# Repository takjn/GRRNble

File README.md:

# GRRNble

DIY Smartwatch using Renesas RL78/G13 MCU and RN4020 ble module with Android companion app.

## Specification
### Hardware

- RL78/G13 32MHz (R5F100LJAFB 64pin LFQFP)
- ROM/RAM: 256KB/20KB
- 0.96″ 128x64 OLED display
- RN4020 Bluetooth Low Energy module
- RTC
- Buzzer
- Measuring battery voltage
- Li-Polymer Charging circuit

### Software

- Arduino like [IDE for GR](http://gadget.renesas.com/en/product/ide4gr.html) based smartwatch app
- [Android companion app](https://play.google.com/store/apps/details?id=com.github.takjn.grrnble)

## Hardware
### Schematic diagram
There is a KiCad project file in KiCad folder. Also, you can see the schematic pdf file in pdf folder.

### Parts list
All capacitors and resistors are 0805 (2012) SMD.

| Reference(s) | Value | Qty | Note |
|:---|:---|:---|:---|
|C1|0.47uF|1|I used 1.0uF insted.|
|C2, C11|0.1uF|2||
|C3, C4|15pF|2||
|C5, C6, C9, C10, C15, C16|1.0uF|6||
|C7, C12, C13|4.7uF|3||
|C8|2.2uF|1|I used 4.7uF insted.|
|R1|1k|1||
|R2|12k|1||
|R3|2k|1||
|R4|390k|1||
|R5, R6, R7, R13|10k|4||
|R8|22k|1||
|R9, R10|47k|2||
|R11|100k|1||
|R12, R14|100R|2||
|R15|7K5|1||
|R16|2K7|1||
|D1|CUS10F30|1||
|Q1, Q3|DMG3415U|2|P-ch FET|
|Q2|BSS138|1|N-ch FET|
|SW1, SW3, SW2|SKSCLAE010|3|ALPS Side Push switch|
|U1|R5F100LJAFB|1|RL78/G13 64pin|
|U2|UGCT7525AN4|1|Buzzer|
|U3|SSD1306|1|OLED 128x64 0.96 inch|
|U4|MCP73831-2-OT|1|Li-Polymer Charge Management Controller|
|U5|RN4020|1|Bluetooth Low Energy module|
|U6|MCP1703A-3302|1|LDO Regulator|
|Y1|FC-135|1|EPSON 3.2 x 1.5 x 0.80mm 32.768k crystal|
|BT1|Li-Po battery|1|3.7V/40mAh|
|J1|JST SH/1.0 6pin connector|1|JST 1.0mm pitch connector|
|-|JST SH/1.0 6pin cable|1|JST 1.0mm pitch terminal cable|
|-|FT232R / FT231X USB to serial adapter|1||

## Software

### RN4020 setup app

RN4020 can be setup with a special program and serial monitor.
Open RN4020Setup folder with [IDE for GR](http://gadget.renesas.com/en/product/ide4gr.html).
Connect your board and select GR-Cotton from "Tools" -> "Board" in the menu.
Compile the program and upload it to the board.

After uploading the sketch, select the port from "Tools" -> "Serial Port" in the menu and open Serial monitor.

### Smartwatch app

Open GRRNble folder with [IDE for GR](http://gadget.renesas.com/en/product/ide4gr.html).
Connect your board and select GR-Cotton from "Tools" -> "Board" in the menu.
Compile the program and upload it to the board.

### Android companion app

You need to have a development environment with Android Studio to build the Android App in the Android folder.

If you don't want to build from source files, you can install the compiled app from [Google Play](https://play.google.com/store/apps/details?id=com.github.takjn.grrnble).

## References
### Libraries
- [https://github.com/greiman/SSD1306Ascii](https://github.com/greiman/SSD1306Ascii)
- [https://github.com/Tamakichi/Arduino-misakiUTF16](https://github.com/Tamakichi/Arduino-misakiUTF16)

### Useful information (EN)
- [Gadget Renesas](http://gadget.renesas.com/en/)
- [GR-COTTON schematic diagram](http://gadget.renesas.com/ja/product/documents/gr-cotton_sch.pdf)
- [RN4020 Bluetooth® Low Energy Module User’s Guide](http://ww1.microchip.com/downloads/en/devicedoc/70005191b.pdf)
- [MCP1703A](http://akizukidenshi.com/download/ds/microchip/mcp1703a.pdf)
- [Designing A Li-Ion Battery Charger and Load Sharing System With
Microchip’s Stand-Alone Li-Ion Battery Charge Management Controller](http://ww1.microchip.com/downloads/en/appnotes/01149c.pdf)

### Useful information (JA)
- [Gadget Renesas](http://gadget.renesas.com/jp/)
- [GR-COTTON回路図](http://gadget.renesas.com/ja/product/documents/gr-cotton_sch.pdf)
- [RL78/G13 低消費電力動作編](https://www.renesas.com/jp/ja/doc/products/mpumcu/apn/rl78/001/r01an0465jj0210_rl78.pdf)
- [RN4020 Bluetooth® Low Energy モジュールユーザガイド](http://akizukidenshi.com/download/ds/microchip/70005191A_JP.pdf)
- [MCP1703A](http://akizukidenshi.com/download/ds/microchip/mcp1703a.pdf)
- [マイクロチップのスタンドアロンリチウムイオンバッテリ充電管理コントローラを使用したリチウムイオンバッテリ充電回路および負荷分担システムの設計](http://ww1.microchip.com/downloads/en/AppNotes/DS01149C_JP_battery.pdf)
- [BLE通信ソフトを作る ( Android Studio 2.3.3 + RN4020 )](http://www.hiramine.com/programming/blecommunicator/index.html)
- [KiCadで雑に基板を作る チュートリアル](https://www.slideshare.net/soburi/kicad-53622272)

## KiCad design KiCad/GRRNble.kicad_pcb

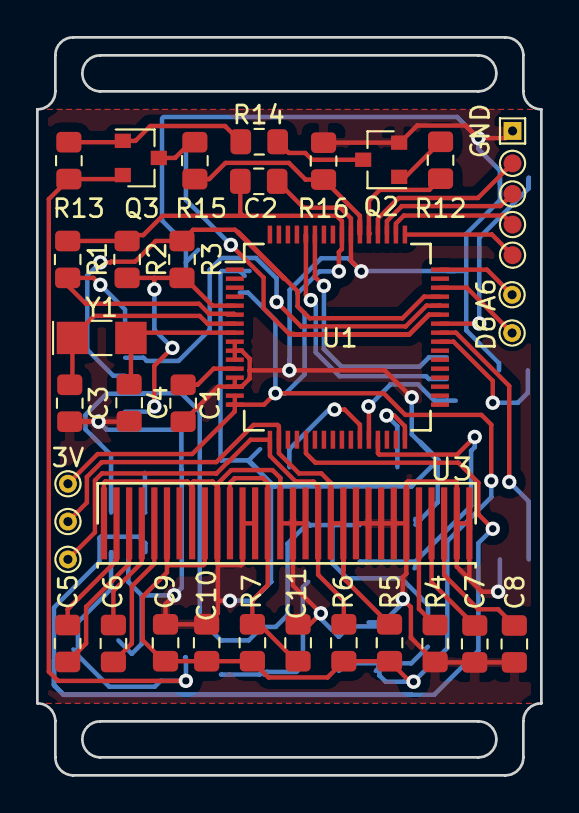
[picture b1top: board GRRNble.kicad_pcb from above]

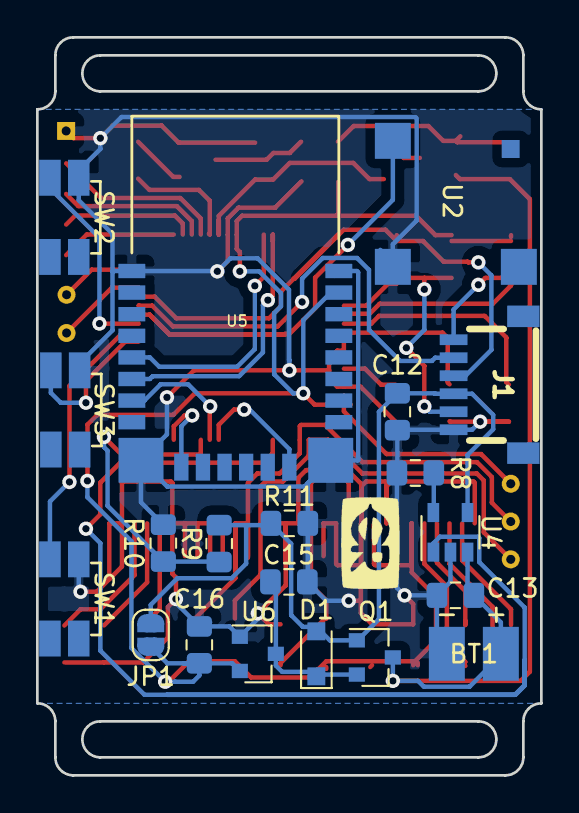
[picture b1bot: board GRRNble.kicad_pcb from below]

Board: 2 copper layers, 28.0 x 41.0 mm, 58 parts (20 on the bottom side), 46 nets.

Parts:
3V: +3V; TestPoint_THTPad_D1.0mm_Drill0.5mm
A2: A2; TestPoint_Pad_D1.0mm
A3: A3; TestPoint_Pad_D1.0mm
A4: A4; TestPoint_Pad_D1.0mm
A5: A5; TestPoint_Pad_D1.0mm
A6: A6; TestPoint_THTPad_D1.0mm_Drill0.5mm
BT1: Battery_Cell; BatteryPad
C1: 0.47uF; C_0805_2012Metric_Pad1.15x1.40mm_HandSolder
C2, C11: 0.1uF; C_0805_2012Metric_Pad1.15x1.40mm_HandSolder
C3, C4: 15pF; C_0805_2012Metric_Pad1.15x1.40mm_HandSolder
C5, C6, C9, C10, C15, C16: 1.0uF; C_0805_2012Metric_Pad1.15x1.40mm_HandSolder
C7, C12, C13: 4.7uF; C_0805_2012Metric_Pad1.15x1.40mm_HandSolder
C8: 2.2uF; C_0805_2012Metric_Pad1.15x1.40mm_HandSolder
D1: CUS10F30; D_SOD-323_HandSoldering
D6: D6; TestPoint_THTPad_D1.0mm_Drill0.5mm
GND: GND; TestPoint_THTPad_1.0x1.0mm_Drill0.5mm
J1: JST_SH_06; JST-SM-06B-SRSS-TB
JP1: Jumper_NO_Small; SolderJumper-2_P1.3mm_Open_RoundedPad1.0x1.5mm
Q1, Q3: DMG3415U; SOT-23
Q2: BSS138; SOT-23
R1: 1k; R_0805_2012Metric_Pad1.15x1.40mm_HandSolder
R2: 12k; R_0805_2012Metric_Pad1.15x1.40mm_HandSolder
R3: 2k; R_0805_2012Metric_Pad1.15x1.40mm_HandSolder
R4: 390k; R_0805_2012Metric_Pad1.15x1.40mm_HandSolder
R5, R6, R7, R13: 10k; R_0805_2012Metric_Pad1.15x1.40mm_HandSolder
R8: 22k; R_0805_2012Metric_Pad1.15x1.40mm_HandSolder
R9, R10: 47k; R_0805_2012Metric_Pad1.15x1.40mm_HandSolder
R11: 100k; R_0805_2012Metric_Pad1.15x1.40mm_HandSolder
R12, R14: 100R; R_0805_2012Metric_Pad1.15x1.40mm_HandSolder
R15: 7K5; R_0805_2012Metric_Pad1.15x1.40mm_HandSolder
R16: 2K7; R_0805_2012Metric_Pad1.15x1.40mm_HandSolder
SCL: SCL; TestPoint_THTPad_D1.0mm_Drill0.5mm
SDA: SDA; TestPoint_THTPad_D1.0mm_Drill0.5mm
SW1, SW2, SW3: SW_Push; SKSC
U1: R5F100LJAFB; LQFP-64_10x10mm_P0.5mm
U2: BUZZER; BZ7025_3pin
U3: SSD1306
U4: MCP73831-2-OT; SOT-23-5
U5: RN4020
U6: MCP1703A-3302_SOT23; SOT-23
Y1: 32.768k; Crystal_SMD_G8-2Pin_3.2x1.5mm_HandSoldering

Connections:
+3V3: 3V.1, C2.1, C9.1, C10.1, C16.1, JP1.2, R1.1, R2.1, R5.1, R6.1, R7.2, U1.15, U1.16, U1.56, U3.6, U3.9, U5.23, U6.2
+5V: C15.1, D1.1, Q1.2, U6.3
+BATT: BT1.1, C13.1, Q1.3, Q3.2, R13.1, U4.3
A2: A2.1, U1.52
A3: A3.1, U1.51
A4: A4.1, U1.50
A5: A5.1, U1.49
A6: A6.1, U1.48
BATT_ENABLE: R12.2, U1.53
BATT_LEVEL: R15.2, R16.1, U1.54
CTS: J1.5, R2.2, R3.1, U1.5
D6: D6.1, U1.46
D7/TXD: U1.60, U5.6
D8/RXD: U1.59, U5.5
DTR: J1.1, R1.2, U1.6
GND: BT1.2, C1.2, C2.2, C3.2, C4.2, C7.2, C8.2, C9.2, C10.2, C11.2, C12.2, C13.2, C15.2, C16.2, GND.1, J1.6, Q2.2, R4.2, R8.2, R10.2, R11.2, R16.2, SW1.2, SW2.2, SW3.2, U1.9, U1.10, U1.11, U1.13, U1.14, U1.55, U2.2, U3.1, U3.8, U3.10, U3.12, U3.13, U3.15, U3.16, U3.17, U3.21, U3.22, U3.23, U3.24, U3.25, U3.29, U3.30, U4.2, U5.1, U5.9, U5.16, U5.24, U6.1
unnamed: C1.1, U1.12
unnamed: C3.1, U1.7, Y1.1
unnamed: C4.1, U1.8, Y1.2
unnamed: C5.1, U3.2
unnamed: C5.2, U3.3
unnamed: C6.1, U3.4
unnamed: C6.2, U3.5
unnamed: C7.1, U3.27
unnamed: C8.1, U3.28
unnamed: C11.1, R7.1, U3.11, U3.14
unnamed: C12.1, D1.2, J1.4, JP1.1, Q1.1, R9.2, R11.1, U4.4
unnamed: Q2.1, R12.1
unnamed: Q2.3, R14.2
unnamed: Q3.1, R13.2, R14.1
unnamed: Q3.3, R15.1
unnamed: R4.1, U3.26
unnamed: R8.1, U4.5
unnamed: U1.43, U2.1
PIO1: U1.32, U5.10
RXD: J1.2, U1.44
SCL: R6.2, SCL.1, U1.17, U3.18
SDA: R5.2, SDA.1, U1.18, U3.19, U3.20
STAT: U1.21, U4.1
SW1: SW1.1, U1.41
SW2: SW2.1, U1.42
SW3: SW3.1, U1.40
TXD: J1.3, R3.2, U1.45
VDD: R9.1, R10.1, U1.29
WAKEHW: U1.27, U5.15
WAKESW: U1.28, U5.7

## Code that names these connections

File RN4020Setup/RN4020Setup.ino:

/**
  GRRNble - RN4020 setup program

  Copyright (c) 2019 Jun Takeda

  This software is released under the MIT License.
  http://opensource.org/licenses/mit-license.php
*/

#include <Arduino.h>

// pin assignments
#define KEY_PREV_PIN    10          // pin for previous button
#define KEY_SELECT_PIN  3           // pin for select button
#define KEY_NEXT_PIN    5           // pin for next button
#define WAKEHW_PIN  11              // pin for RN4020 WAKEHW
#define WAKESW_PIN  12              // pin for RN4020 WAKESW
#define PIO1_PIN 2                  // pin for RN4020 PIO1

// key code
#define KEY_NONE 0
#define KEY_PREV 1
#define KEY_NEXT 2
#define KEY_SELECT 3


int waitKeyIn() {
  while (digitalRead(KEY_SELECT_PIN) != 0 && digitalRead(KEY_PREV_PIN) != 0 && digitalRead(KEY_NEXT_PIN) != 0);

  if (digitalRead(KEY_SELECT_PIN) == 0) {
    while (digitalRead(KEY_SELECT_PIN) == 0);
    return KEY_SELECT;
  } else if (digitalRead(KEY_PREV_PIN) == 0) {
    while (digitalRead(KEY_PREV_PIN) == 0);
    return KEY_PREV;
  } else if (digitalRead(KEY_NEXT_PIN) == 0) {
    while (digitalRead(KEY_NEXT_PIN) == 0);
    return KEY_NEXT;
  }
  
  return KEY_NONE;
}

void readFromRN4020() {
  while (Serial1.available()) {
    int inByte = Serial1.read();
    Serial.write(inByte); 
    delay(5);
  }
}

void sendToRN4020(String command) {
  Serial1.println(command);
  Serial1.flush();
  delay(500);
  readFromRN4020();
}

void setupRN4020() {
  sendToRN4020("SF,2");            // Factory reset
  sendToRN4020("SN,GRRNble");      // Set name
  sendToRN4020("SB,0");            // Set 2400bps

  sendToRN4020("SS,C0000001");     // Enable device information, battery, private service
  sendToRN4020("SR,25002000");     // Set the device as periferal (Auto Advertise, No Direct Advertisement, Run script after power on)
  sendToRN4020("ST,0010,0004,0258");    // Set interval, latency and timeout
  sendToRN4020("PZ");              // Clear the current private service and characteristics

  // Set private service UUID
  sendToRN4020("PS,3B382559223F48CA81B4E151598F661B");

  // Add private characteristic to current private service.
  // The property of this characteristic is 0x12 (readble and could notify) and has a maximum data size of 2 bytes.
  sendToRN4020("PC,DB5445C44A70442287AF81D35456BEB5,12,02");

  // The property of this characteristic is 0x0A (readble and writable) and has a maximum data size of 20 bytes.
  sendToRN4020("PC,B23324431DD3407BB3E65D349CAF5368,0A,14");
  sendToRN4020("PC,E2B8D854BFA64E798A5326B07604597D,0A,14");

  // The property of this characteristic is 0x04 (writable) and has a maximum data size of 1 bytes.
  sendToRN4020("PC,4344EEE2C4674318BFAB7564815A5DB8,04,01");

  sendToRN4020("WC");              // Clear script
  sendToRN4020("WW");              // Enter script input mode

  // write RN4020 script
  sendToRN4020("@PW_ON");          // handle power on event
  sendToRN4020("|O,01,%001F");     // associate handle 0x001F to PIO1

  // send the “ESC” key to exit from script input mode.
  Serial1.write(0x1b);
  Serial1.flush();

  sendToRN4020("R,1");             // Reboot RN4020 to make the changes effective

  Serial1.begin(2400);
  delay(1000);
  sendToRN4020("WP");              // Pause script

  sendToRN4020("D");               // Dump configuration
  sendToRN4020("LS");              // list the services on server side. Private service and characteristics could be found in the list
  sendToRN4020("LW");              // Show script
}

void showMenu() {
  Serial.println("--------------------------------------------------------------------------------");
  Serial.println("GRRNble RN4020 setup program");
  Serial.println("--------------------------------------------------------------------------------");
  Serial.println("To connect with RN4020 at 115200 bps(default), push the top button.");
  Serial.println("To connect with RN4020 at 2400 bps, push the bottom button.");

  int key = waitKeyIn();
  if (key == KEY_NEXT) {
    Serial1.begin(2400);
    Serial.println("2400 bps is selected.");
  } else {
    Serial.println("115200 bps is selected.");
  }
  Serial.println("");
  sendToRN4020("WP");
  sendToRN4020("D");
  Serial.println("");

  Serial.println("To setup, push the top button.");
  Serial.println("To communicate with RN4020, push the bottom button.");
  Serial.println("To restart, push the center button.");

  key = waitKeyIn();
  if (key == KEY_PREV) {
    Serial.println("Starting setup.");
    setupRN4020();
  }
  if (key == KEY_SELECT) {
    softwareReset();
  } 

  Serial.println("");
}

bool interrupted = false;
void debugInterrupt() {
  interrupted = true;
}

void setup() {
  pinMode(KEY_PREV_PIN, INPUT_PULLUP);
  pinMode(KEY_SELECT_PIN, INPUT_PULLUP);
  pinMode(KEY_NEXT_PIN, INPUT_PULLUP);

  // set RN4020 power status
  pinMode(PIO1_PIN, INPUT);
  pinMode(WAKEHW_PIN, OUTPUT);
  pinMode(WAKESW_PIN, OUTPUT);
  digitalWrite(WAKEHW_PIN, LOW);
  digitalWrite(WAKESW_PIN, HIGH);

  Serial.begin(115200);
  Serial1.begin(115200);

  showMenu();

  attachInterrupt(0, debugInterrupt, RISING);
  Serial.println("Done.You can communicate with RN4020.");
}

void loop() {
  // read from port 1, send to port 0:
  if (Serial1.available()) {
    int inByte = Serial1.read();
    Serial.write(inByte); 
  }
  
  // read from port 0, send to port 1:
  if (Serial.available()) {
    int inByte = Serial.read();
    Serial1.write(inByte); 
  }

  if (interrupted) {
    interrupted = false;
    Serial.println("triggered");
    sendToRN4020("WP");             // Pause script
    sendToRN4020("SHW,001F,00");    // Reset characteristic value
    sendToRN4020("|O,01,00");       // Reset pio0 value
    sendToRN4020("SHR,001B");       // Read characteristic value
    sendToRN4020("WR");             // Run script
  }
}

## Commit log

2018-05-27 init
2018-05-27 add check BLE
2018-05-27 add README
2018-05-27 add device list
2018-05-27 add read characteristic
2018-05-27 add characteristic changed
2018-05-27 add write characteristic
2018-05-27 add notification listener service
2018-05-28 Rearrange and reformat code
2018-05-30 change folder structure
2018-05-30 add KiCad project
2018-05-30 add IDE4GR project
2018-06-01 add BLE support
2018-06-01 add Battery level service
2018-06-01 some improvement
2018-06-01 bug fix
2018-06-02 fix BLE handler
2018-06-02 refactoring
2018-06-02 change from listening to pooling
2018-06-04 improve UI
2018-06-04 add battery level
2018-06-05 add temperature service
2018-06-05 add progress bar
2018-06-05 add debug option and icons
2018-06-05 add time sync menu
2018-06-06 add time sync handler
2018-06-09 change pin assign
2018-06-09 do not hide debug fragment
2018-06-10 add BLE service
2018-06-11 add misakiUTF16 library
2018-06-11 show notification in the watch mode
2018-06-11 change notification message
2018-06-13 WIP (PCB)
2018-06-14 update PCB
2018-06-17 stability improments
2018-06-17 stability improvement
2018-06-17 add PhoneCallReceiver
2018-06-18 change application logo
2018-06-20 set power management mode
2018-06-20 add stanby loop
2018-06-21 add disable charge pump
2018-06-21 improve power consumption
2018-06-21 always on
2018-06-21 add stanby disp setting
2018-06-21 some improvements
2018-06-22 change targetSdkVersion
2018-06-22 update version
2018-06-26 fix potential memory leak
2018-06-27 add time sync on connected
2018-06-30 add extra message
2018-07-13 fix max voltage
2018-07-14 add PDF file
2019-02-09 add intrrupt handler
2019-02-14 change schematic layout
2019-02-14 change PCB status
2019-02-14 change PCB layout
2019-02-14 update gerber files
2019-03-01 change pin assignments
2019-03-01 add RN4020 setup program
2019-03-01 refactoring main loop
2019-03-01 remove unnecessarily global functions
2019-03-01 remove unnecessary global variable
2019-03-01 remove unnecessary global variables
2019-03-01 fix SSD1306 power off sequence
2019-03-02 add private characteristic
2019-03-02 bump up version number to 4.
2019-03-04 add schematic
2019-03-09 add check USB status
2019-03-10 parameter tuning
2019-03-10 update PDF file
2019-03-13 set BLE interval, latency and timeout
2019-03-14 add game mode
2019-03-14 add STL files
2019-03-20 WIP:Change schematic
2019-03-22 change PIN assignment
2019-03-22 update schematic pdf
2019-03-22 add PCB images
2019-03-24 energy consumption reduction
2019-03-24 add gitignore
2019-03-24 add serial enable/disable
2019-03-31 change key assignment
